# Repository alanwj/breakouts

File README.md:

Breakouts
---------
A collection of breakout boards.

Structure
---------
Each breakout board is in its own subdirectory.  All packages, symbols, and devices are in breakouts.lbr in the repository root.

Where applicable, datasheets and photos of fabricated boards are included.

Index
-----
- ATX12V\_MAIN\_VERT - Verical motherboard connector for ATX12V power supplies
- SOT23-3 - Small outline transistor package with 3 leads
- SOT23-5 - Small outline transistor package with 5 leads

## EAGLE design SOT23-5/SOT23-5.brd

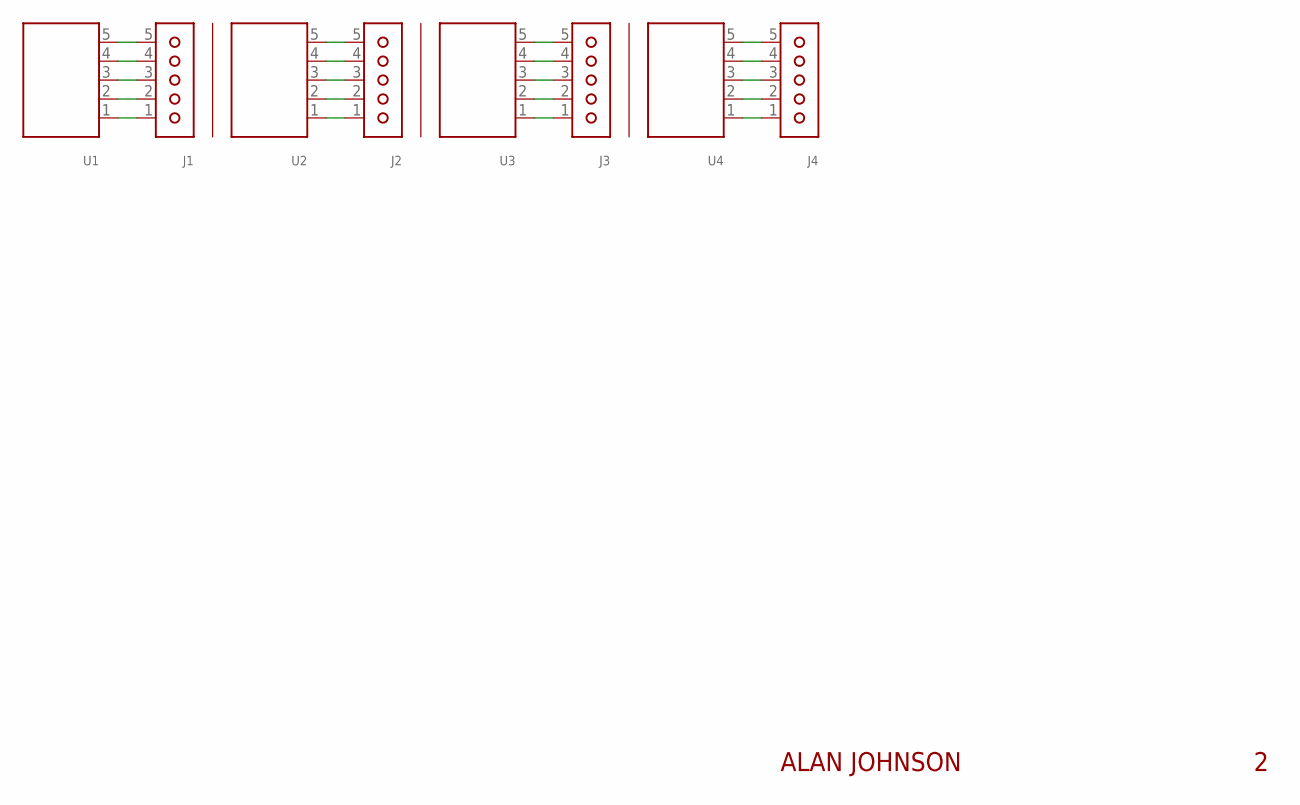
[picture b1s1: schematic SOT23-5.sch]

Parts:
J1, J2, J3, J4: 1X05
U1, U2, U3, U4: SOT23-5

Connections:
unnamed: J1.1, U1.1
unnamed: J1.2, U1.2
unnamed: J1.3, U1.3
unnamed: J2.1, U2.1
unnamed: J2.2, U2.2
unnamed: J2.3, U2.3
unnamed: J3.1, U3.1
unnamed: J3.2, U3.2
unnamed: J3.3, U3.3
unnamed: J4.1, U4.1
unnamed: J4.2, U4.2
unnamed: J4.3, U4.3
unnamed: J1.4, U1.4
unnamed: J1.5, U1.5
unnamed: J2.4, U2.4
unnamed: J2.5, U2.5
unnamed: J3.4, U3.4
unnamed: J3.5, U3.5
unnamed: J4.4, U4.4
unnamed: J4.5, U4.5

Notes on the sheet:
ALAN JOHNSON

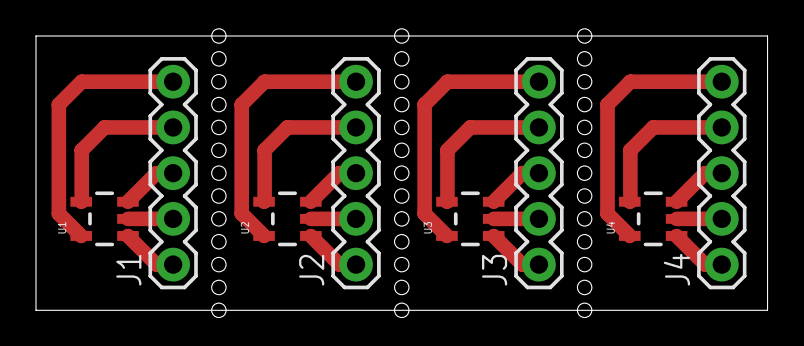
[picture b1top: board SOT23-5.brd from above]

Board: 2 copper layers, 40.6 x 15.2 mm, 8 parts (0 on the bottom side), 20 nets.

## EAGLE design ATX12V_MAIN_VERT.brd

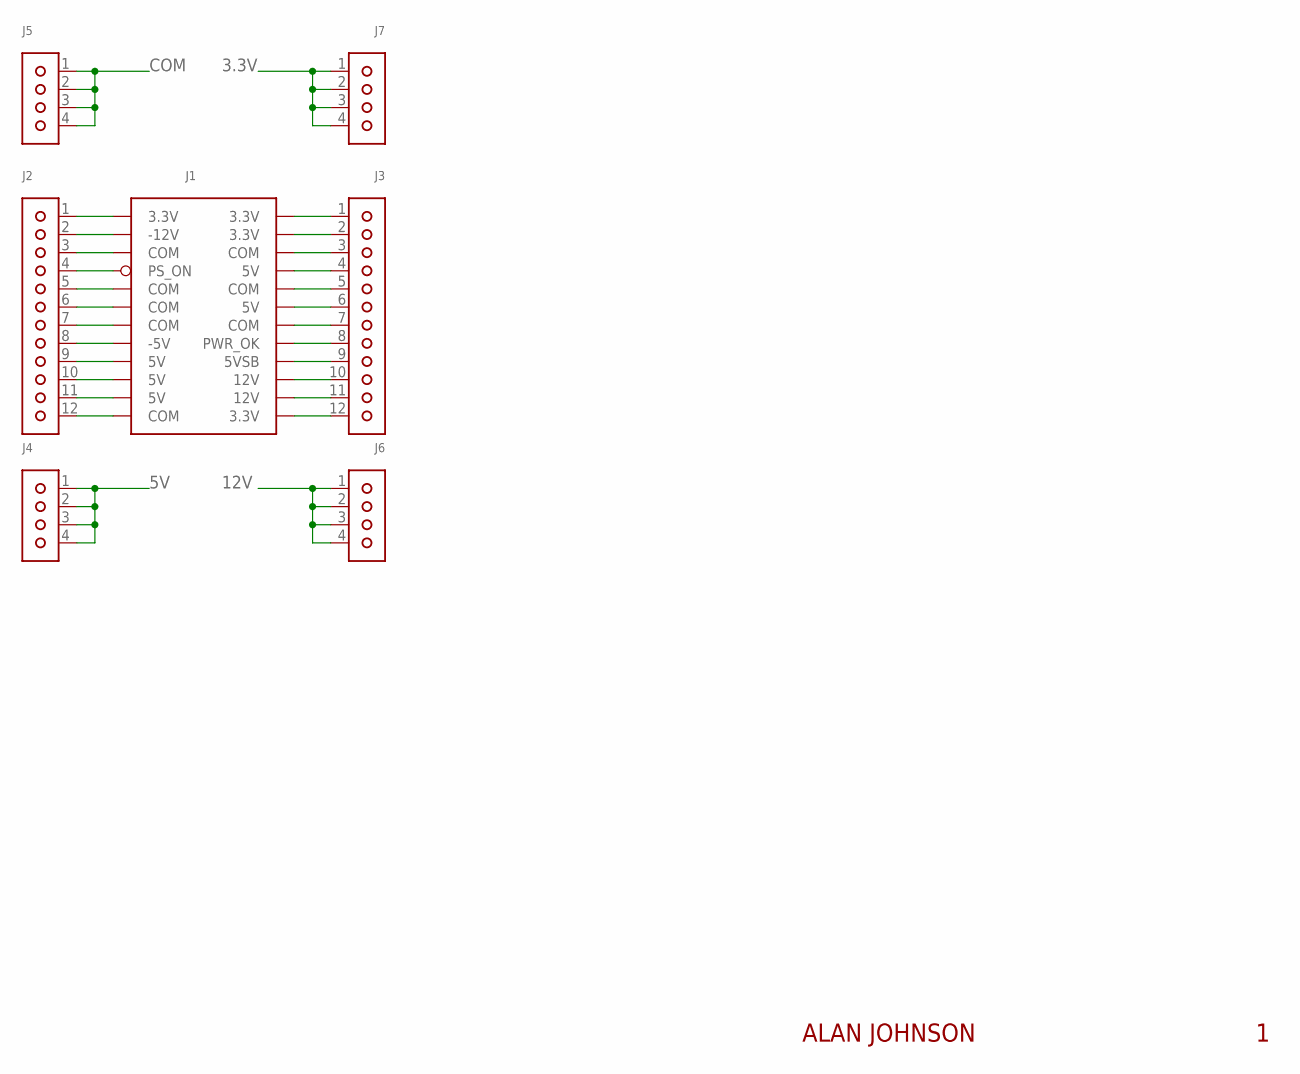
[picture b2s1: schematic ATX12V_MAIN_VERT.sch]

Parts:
J1: ATX12V_MAIN_VERT; 44206-0007
J2, J3: 1X12
J4, J5, J6, J7: 1X04

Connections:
3.3V: J1.1 (3.3V), J1.2 (3.3V), J1.12 (3.3V), J1.13 (3.3V), J2.1, J3.1, J3.2, J3.12, J7.1, J7.2, J7.3, J7.4
5V: J1.4 (5V), J1.6 (5V), J1.21 (5V), J1.22 (5V), J1.23 (5V), J2.9, J2.10, J2.11, J3.4, J3.6, J4.1, J4.2, J4.3, J4.4
5VSB: J1.9 (5VSB), J3.9
12V: J1.10 (12V), J1.11 (12V), J3.10, J3.11, J6.1, J6.2, J6.3, J6.4
-5V: J1.20 (-5V), J2.8
-12V: J1.14 (-12V), J2.2
COM: J1.3 (COM), J1.5 (COM), J1.7 (COM), J1.15 (COM), J1.17 (COM), J1.18 (COM), J1.19 (COM), J1.24 (COM), J2.3, J2.5, J2.6, J2.7, J2.12, J3.3, J3.5, J3.7, J5.1, J5.2, J5.3, J5.4
PS_ON: J1.16 (PS_ON), J2.4
PWR_OK: J1.8 (PWR_OK), J3.8

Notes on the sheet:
ALAN JOHNSON

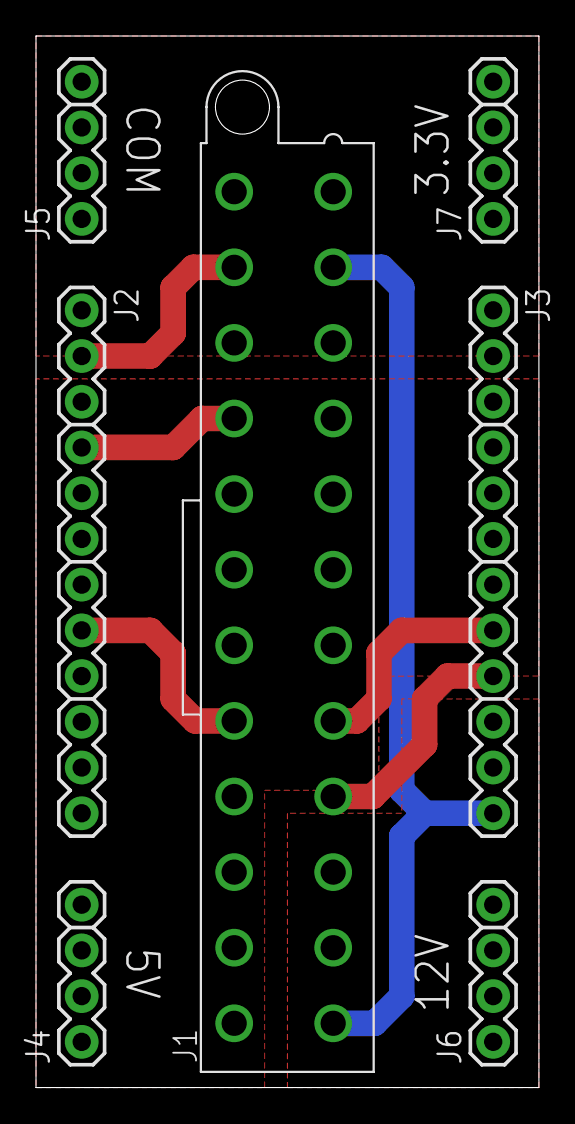
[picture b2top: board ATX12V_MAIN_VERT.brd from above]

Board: 2 copper layers, 27.9 x 58.4 mm, 7 parts (0 on the bottom side), 9 nets.

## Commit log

2014-10-08 New eagle project for breakout boards.
2014-10-08 Add DRU based on OSH park PCB rules.
2014-10-08 Add an SOT23-3 breakout.
2014-10-09 Add a CAM file based on OSH park defaults, removing names from the silk layers.
2014-10-09 Add breakout for ATX12V main connector (vertical).
2014-10-11 Added an SOT23-5 breakout.
2014-10-21 Fix some silk screen flaws in pin header devices.
2014-10-21 Ignore Eagle temporary files.
2014-10-21 Move each board to its own subfolder.
2014-10-21 Add a README.
